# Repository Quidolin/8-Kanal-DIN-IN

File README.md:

# 8-Kanal-DIN-IN
Switch and LED addon board for 8-Kanal-DIN-BASE
for HomeMatic HM-MOD-EM-8 8-channel input module
Eagle-project

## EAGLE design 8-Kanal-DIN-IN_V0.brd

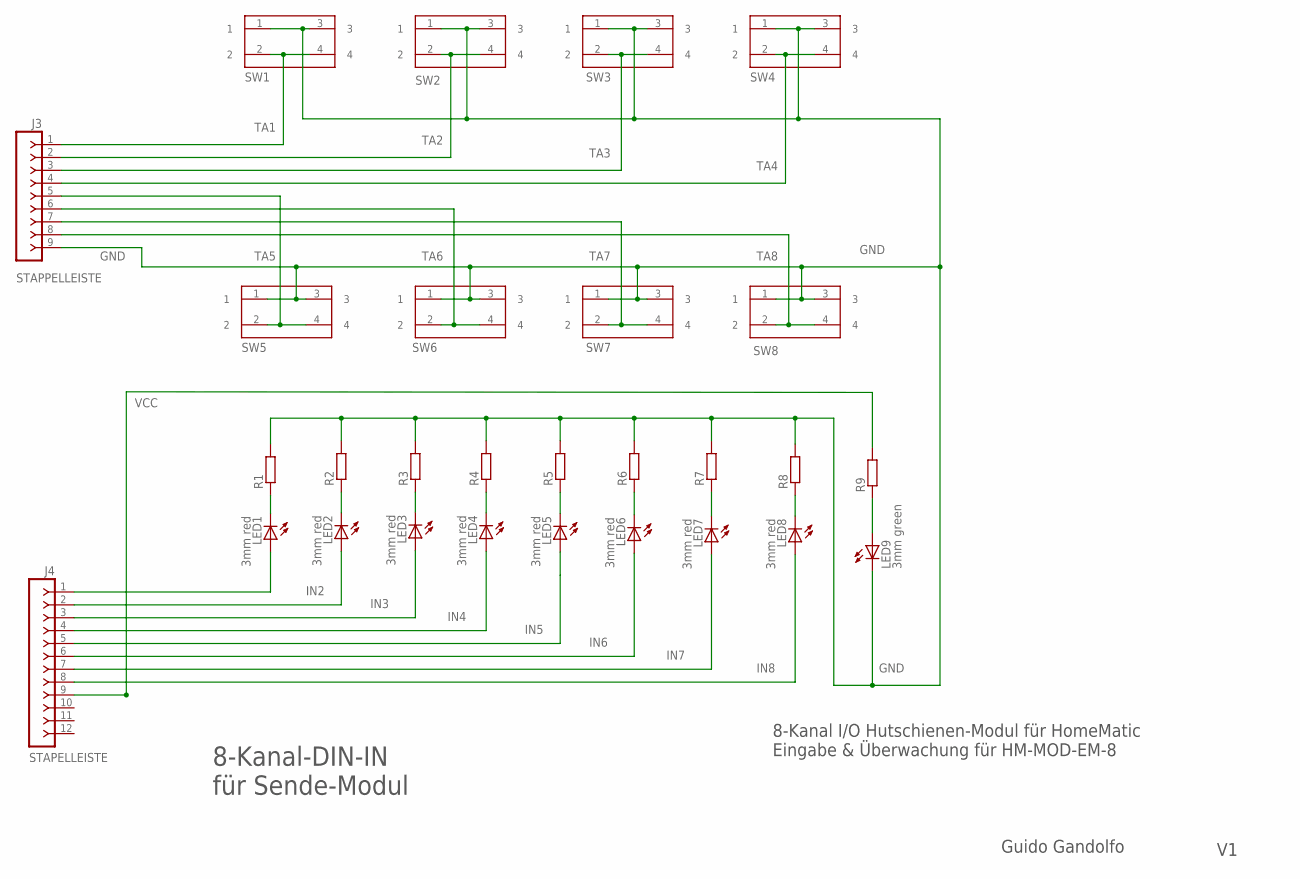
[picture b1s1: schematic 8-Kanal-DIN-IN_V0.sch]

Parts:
J3: STAPPELLEISTE; SIP-100-09-40Y
J4: STAPELLEISTE; SIP-100-12-40Y
LED1, LED2, LED3, LED4, LED5, LED6, LED7, LED8: 3mm red; LED3MM
LED9: 3mm green; LED3MM
R1, R2, R3, R4, R5, R6, R7, R8, R9: R-EU_0207/2V; 0207/2V
SW1, SW2, SW3, SW4, SW5, SW6, SW7, SW8: TASTER 9305; 430156130936

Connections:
GND: J3.9, LED9.K (C), R1.2, R2.2, R3.2, R4.2, R5.2, R6.2, R7.2, R8.2, SW1.1, SW1.3, SW2.1, SW2.3, SW3.1, SW3.3, SW4.1, SW4.3, SW5.1, SW5.3, SW6.1, SW6.3, SW7.1, SW7.3, SW8.1, SW8.3
IN1: J4.1, LED1.A
IN2: J4.2, LED2.A
IN3: J4.3, LED3.A
IN4: J4.4, LED4.A
IN5: J4.5, LED5.A
IN6: J4.6, LED6.A
IN7: J4.7, LED7.A
IN8: J4.8, LED8.A
unnamed: LED1.K (C), R1.1
unnamed: LED2.K (C), R2.1
unnamed: LED3.K (C), R3.1
unnamed: LED4.K (C), R4.1
unnamed: LED5.K (C), R5.1
unnamed: LED6.K (C), R6.1
unnamed: LED7.K (C), R7.1
unnamed: LED8.K (C), R8.1
unnamed: LED9.A, R9.1
TA1: J3.1, SW1.2, SW1.4
TA2: J3.2, SW2.2, SW2.4
TA3: J3.3, SW3.2, SW3.4
TA4: J3.4, SW4.2, SW4.4
TA5: J3.5, SW5.2, SW5.4
TA6: J3.6, SW6.2, SW6.4
TA7: J3.7, SW7.2, SW7.4
TA8: J3.8, SW8.2, SW8.4
VCC: J4.9, R9.2

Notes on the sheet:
8-Kanal-DIN-IN für Sende-Modul
8-Kanal I/O Hutschienen-Modul für HomeMatic Eingabe & Überwachung für HM-MOD-EM-8
Guido Gandolfo

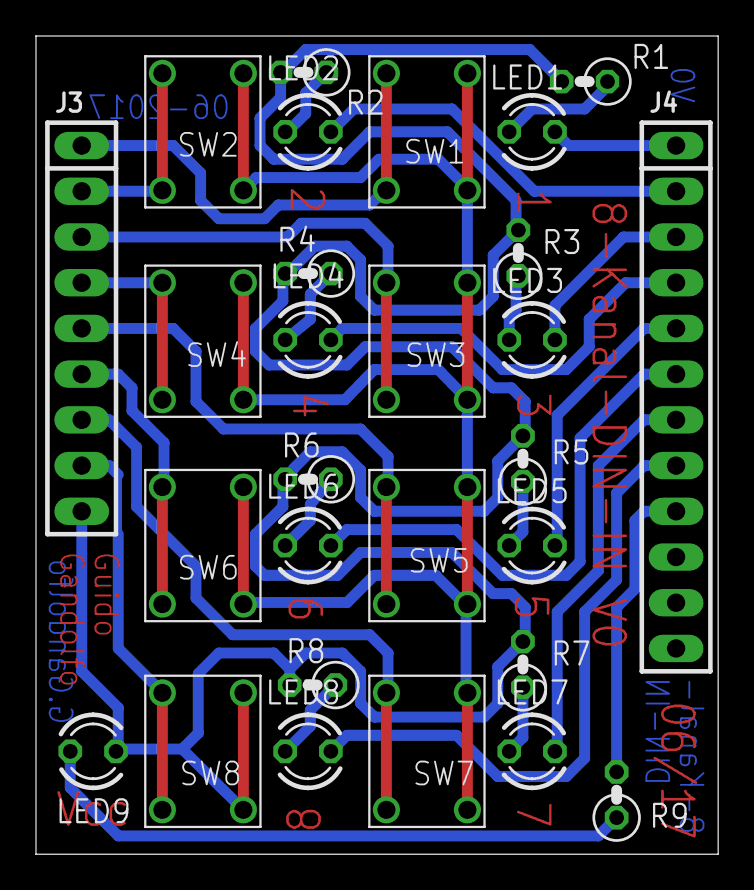
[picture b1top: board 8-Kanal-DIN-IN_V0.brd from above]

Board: 2 copper layers, 37.9 x 45.5 mm, 28 parts (0 on the bottom side), 27 nets.

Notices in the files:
parts and their libraries:
con-headers-jp: Copyright (C) 2008, Bob Starr
Switch_rev16b_wurth: Copyright: Würth Elektronik
